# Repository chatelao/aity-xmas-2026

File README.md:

# AITY Xmas Tree 2026

An interactive Christmas tree PCB designed to work with either a **Seeed Studio XIAO RP2040** or a **Seeed Studio XIAO ESP32-C6** microcontroller module, featuring 60 addressable NeoPixel LEDs, a piezo speaker/buzzer, and test point outputs.

## Hardware Specifications

- **Microcontroller:** Seeed Studio XIAO RP2040 or Seeed Studio XIAO ESP32-C6
- **LEDs:** 60 x WS2812B NeoPixel RGB LEDs connected to pin `D10`
- **Audio:** Speaker/Buzzer connected to pin `D0`
- **Test Points:** TP101 – TP109 connected to pins `D1` – `D9`

## ASCII Pinout Diagram

Both XIAO boards share the same standard XIAO form factor and 14-pin pinout:

```
                       +-------------------+
                       |   USB-C           |
                       |  [ Seeed XIAO ]   |
                       | [RP2040/ESP32-C6] |
(Speaker LS101) D0/A0 -| [1]          [14] |- 5V (VDD Power)
 (TestPoint 1)  D1/A1 -| [2]          [13] |- GND
 (TestPoint 3)  D2/A2 -| [3]          [12] |- 3V3 (NC)
 (TestPoint 4)  D3/A3 -| [4]          [11] |- D10/MOSI (60 x NeoPixel LEDs)
 (TestPoint 5) D4/SDA -| [5]          [10] |- D9/MISO  (TestPoint 2)
 (TestPoint 8) D5/SCL -| [6]           [9] |- D8/SCK   (TestPoint 7)
 (TestPoint 6)  D6/TX -| [7]           [8] |- D7/RX    (TestPoint 9)
                       +-------------------+
```

### Pin Mapping Table

| Pin Number | XIAO Pin Name | RP2040 GPIO | ESP32-C6 GPIO | CircuitPython Pin | Connection / Function |
|------------|---------------|-------------|---------------|-------------------|-----------------------|
| 1          | A0 / D0       | GPIO26      | GPIO0 / PA02  | `board.D0`        | Speaker (LS101)       |
| 2          | A1 / D1       | GPIO27      | GPIO1 / PA04  | `board.D1`        | TestPoint 1 (TP101)   |
| 3          | A2 / D2       | GPIO28      | GPIO2 / PA10  | `board.D2`        | TestPoint 3 (TP103)   |
| 4          | A3 / D3       | GPIO29      | GPIO3 / PA11  | `board.D3`        | TestPoint 4 (TP104)   |
| 5          | SDA / D4      | GPIO6       | GPIO19 / PA08 | `board.D4`        | TestPoint 5 (TP105)   |
| 6          | SCL / D5      | GPIO7       | GPIO20 / PA09 | `board.D5`        | TestPoint 8 (TP108)   |
| 7          | TX / D6       | GPIO0       | GPIO21 / PB08 | `board.D6`        | TestPoint 6 (TP106)   |
| 8          | RX / D7       | GPIO1       | GPIO22 / PB09 | `board.D7`        | TestPoint 9 (TP109)   |
| 9          | SCK / D8      | GPIO2       | GPIO23 / PA07 | `board.D8`        | TestPoint 7 (TP107)   |
| 10         | MISO / D9     | GPIO4       | GPIO9 / PA05  | `board.D9`        | TestPoint 2 (TP102)   |
| 11         | MOSI / D10    | GPIO3       | GPIO18 / PA06 | `board.D10`       | NeoPixel LEDs Data In |
| 12         | 3V3           | 3V3         | 3V3           | `board.3V3`       | Unconnected (NC)      |
| 13         | GND           | GND         | GND           | `board.GND`       | Ground                |
| 14         | 5V            | 5V          | 5V            | `board.5V`        | 5V Power (VDD)        |

---

## Platform Setup & Installation Guides

Detailed instructions on how to install CircuitPython (web-only method) and transfer files (via web browser or file explorer) for each platform:

- [**HOWTO_RP2040.md**](HOWTO_RP2040.md) — Guide for **Seeed Studio XIAO RP2040**
- [**HOWTO_ESP32-C6.md**](HOWTO_ESP32-C6.md) — Guide for **Seeed Studio XIAO ESP32-C6**

---

## Example CircuitPython Script: Rainbow Animation

Save the following script as `code.py` or `main.py` on the target device. Make sure the Adafruit `neopixel` library (`neopixel.mpy`) is placed in the `lib/` folder.

```python
import time
import board
import neopixel

# Try importing built-in colorwheel from rainbowio, fallback if not present
try:
    from rainbowio import colorwheel
except ImportError:
    def colorwheel(pos):
        """Generate rainbow colors across 0-255 positions."""
        pos = int(pos) % 256
        if pos < 85:
            return (pos * 3, 255 - pos * 3, 0)
        elif pos < 170:
            pos -= 85
            return (255 - pos * 3, 0, pos * 3)
        else:
            pos -= 170
            return (0, pos * 3, 255 - pos * 3)

# Configuration
NUM_LEDS = 60
DATA_PIN = board.D10
BRIGHTNESS = 0.3  # Adjust brightness (0.0 to 1.0)

# Initialize NeoPixel strip
pixels = neopixel.NeoPixel(
    DATA_PIN,
    NUM_LEDS,
    brightness=BRIGHTNESS,
    auto_write=False
)

def rainbow_cycle(wait=0.01):
    """Animate a smooth moving rainbow across all 60 LEDs."""
    for j in range(256):
        for i in range(NUM_LEDS):
            pixel_index = (i * 256 // NUM_LEDS) + j
            pixels[i] = colorwheel(pixel_index & 255)
        pixels.show()
        time.sleep(wait)

print("Starting Rainbow Animation on 60 NeoPixel LEDs...")

while True:
    rainbow_cycle(wait=0.01)
```

## Setup Instructions

1. Install CircuitPython on your board (see [HOWTO_RP2040.md](HOWTO_RP2040.md) for XIAO RP2040 or [HOWTO_ESP32-C6.md](HOWTO_ESP32-C6.md) for XIAO ESP32-C6).
2. Obtain the Adafruit CircuitPython Library Bundle (or use the pre-packaged files in `circuitpython/default/`).
3. Copy `neopixel.mpy` into the `lib/` directory on the target board (using file explorer for RP2040 or web workflow for ESP32-C6).
4. Save the example script above (or `circuitpython/default/code.py`) as `code.py` on the target board.

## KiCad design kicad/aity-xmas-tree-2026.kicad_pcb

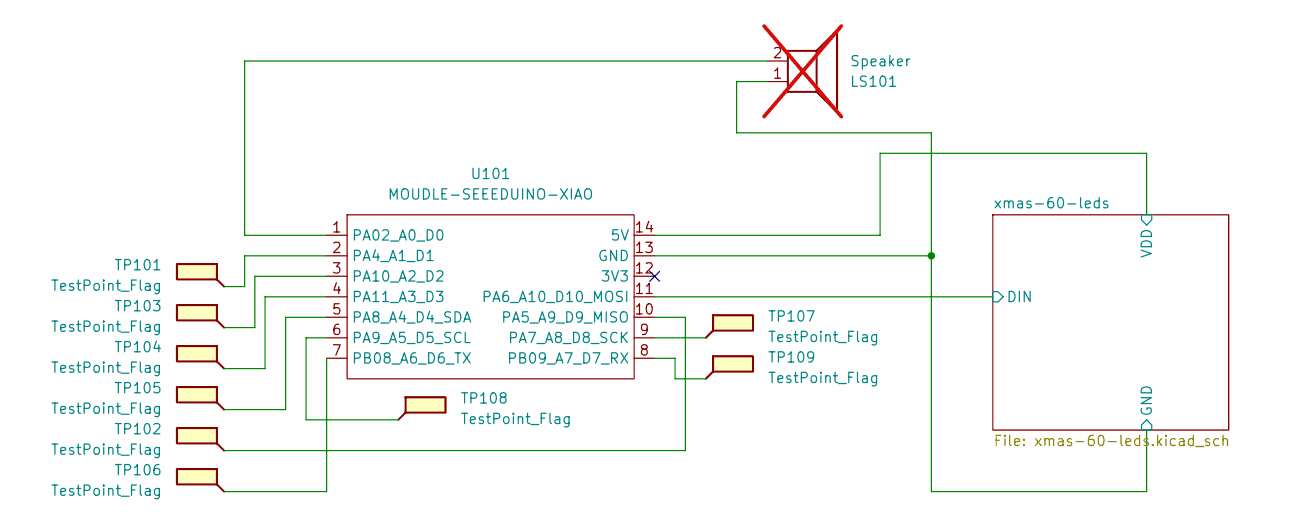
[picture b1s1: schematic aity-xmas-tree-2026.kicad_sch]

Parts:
LS101: Speaker; MagneticBuzzer_CUI_CMT-8504-100-SMT; not fitted
TP101, TP102, TP103, TP104, TP105, TP106, TP107, TP108, TP109: TestPoint_Flag; Kugel
U101: MOUDLE-SEEEDUINO-XIAO; MCU_Seeed_ESP32C3

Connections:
/xmas-60-leds/DIN: U101.11 (PA6_A10_D10_MOSI); also elsewhere on the board
/xmas-60-leds/GND: LS101.1, U101.13 (GND); also elsewhere on the board
/xmas-60-leds/VDD: U101.14 (5V); also elsewhere on the board
unnamed: LS101.2, U101.1 (PA02_A0_D0)
unnamed: TP101.1, U101.2 (PA4_A1_D1)
unnamed: TP102.1, U101.10 (PA5_A9_D9_MISO)
unnamed: TP107.1, U101.9 (PA7_A8_D8_SCK)
unnamed: TP105.1, U101.5 (PA8_A4_D4_SDA)
unnamed: TP108.1, U101.6 (PA9_A5_D5_SCL)
unnamed: TP103.1, U101.3 (PA10_A2_D2)
unnamed: TP104.1, U101.4 (PA11_A3_D3)
unnamed: TP106.1, U101.7 (PB08_A6_D6_TX)
unnamed: TP109.1, U101.8 (PB09_A7_D7_RX)

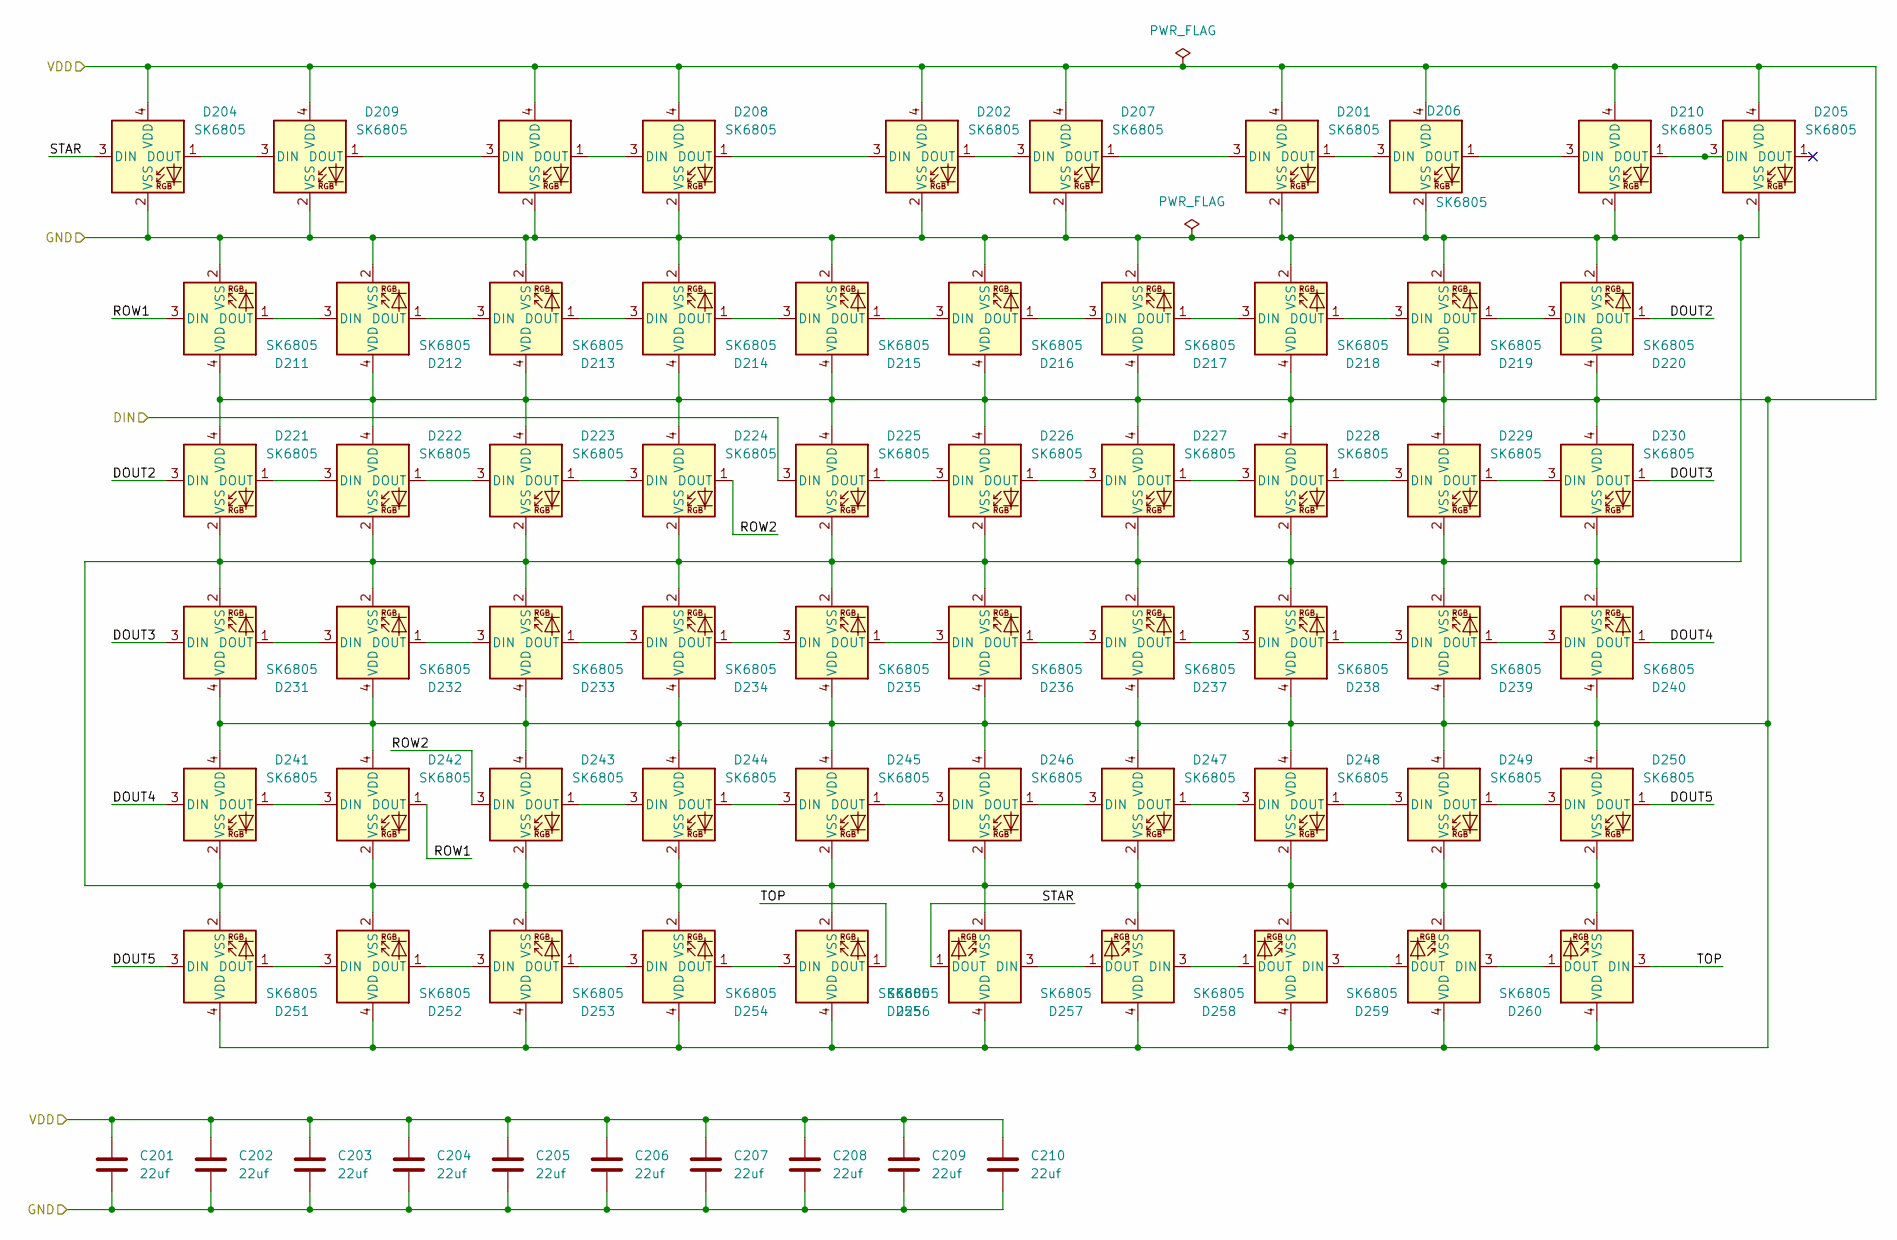
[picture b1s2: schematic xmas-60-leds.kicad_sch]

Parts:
C201, C202, C203, C204, C205, C206, C207, C208, C209, C210: 22uf; C_0603_1608Metric
D201, D203, D204, D205, D207, D208, D209, D210, D211, D212, D213, D214, D215, D216, D217, D218, D219, D220, D221, D222, D223, D224, D225, D226, D227, D228, D229, D230, D231, D232, D233, D234, D235, D236, D237, D238, D239, D240, D241, D242, D243, D244, D245, D246, D247, D248, D249, D250, D251, D252, D253, D254, D255, D256, D257, D258, D259, D260: SK6805; LED_SK6812_1.5x1.5mm
D202, D206: SK6805; LED_SK6805_PLCC4_2.4x2.7mm_P1.3mm

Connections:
/xmas-60-leds/DIN: D225.3 (DIN); also elsewhere on the board
/xmas-60-leds/DOUT2: D220.1 (DOUT), D221.3 (DIN)
/xmas-60-leds/DOUT3: D230.1 (DOUT), D231.3 (DIN)
/xmas-60-leds/DOUT4: D240.1 (DOUT), D241.3 (DIN)
/xmas-60-leds/DOUT5: D250.1 (DOUT), D251.3 (DIN)
/xmas-60-leds/GND: C201.2, C202.2, C203.2, C204.2, C205.2, C206.2, C207.2, C208.2, C209.2, C210.2, D201.2 (VSS), D202.2 (VSS), D203.2 (VSS), D204.2 (VSS), D205.2 (VSS), D206.2 (VSS), D207.2 (VSS), D208.2 (VSS), D209.2 (VSS), D210.2 (VSS), D211.2 (VSS), D212.2 (VSS), D213.2 (VSS), D214.2 (VSS), D215.2 (VSS), D216.2 (VSS), D217.2 (VSS), D218.2 (VSS), D219.2 (VSS), D220.2 (VSS), D221.2 (VSS), D222.2 (VSS), D223.2 (VSS), D224.2 (VSS), D225.2 (VSS), D226.2 (VSS), D227.2 (VSS), D228.2 (VSS), D229.2 (VSS), D230.2 (VSS), D231.2 (VSS), D232.2 (VSS), D233.2 (VSS), D234.2 (VSS), D235.2 (VSS), D236.2 (VSS), D237.2 (VSS), D238.2 (VSS), D239.2 (VSS), D240.2 (VSS), D241.2 (VSS), D242.2 (VSS), D243.2 (VSS), D244.2 (VSS), D245.2 (VSS), D246.2 (VSS), D247.2 (VSS), D248.2 (VSS), D249.2 (VSS), D250.2 (VSS), D251.2 (VSS), D252.2 (VSS), D253.2 (VSS), D254.2 (VSS), D255.2 (VSS), D256.2 (VSS), D257.2 (VSS), D258.2 (VSS), D259.2 (VSS), D260.2 (VSS); also elsewhere on the board
/xmas-60-leds/ROW1: D211.3 (DIN), D242.1 (DOUT)
/xmas-60-leds/ROW2: D224.1 (DOUT), D243.3 (DIN)
/xmas-60-leds/STAR: D204.3 (DIN), D256.1 (DOUT)
/xmas-60-leds/TOP: D255.1 (DOUT), D260.3 (DIN)
/xmas-60-leds/VDD: C201.1, C202.1, C203.1, C204.1, C205.1, C206.1, C207.1, C208.1, C209.1, C210.1, D201.4 (VDD), D202.4 (VDD), D203.4 (VDD), D204.4 (VDD), D205.4 (VDD), D206.4 (VDD), D207.4 (VDD), D208.4 (VDD), D209.4 (VDD), D210.4 (VDD), D211.4 (VDD), D212.4 (VDD), D213.4 (VDD), D214.4 (VDD), D215.4 (VDD), D216.4 (VDD), D217.4 (VDD), D218.4 (VDD), D219.4 (VDD), D220.4 (VDD), D221.4 (VDD), D222.4 (VDD), D223.4 (VDD), D224.4 (VDD), D225.4 (VDD), D226.4 (VDD), D227.4 (VDD), D228.4 (VDD), D229.4 (VDD), D230.4 (VDD), D231.4 (VDD), D232.4 (VDD), D233.4 (VDD), D234.4 (VDD), D235.4 (VDD), D236.4 (VDD), D237.4 (VDD), D238.4 (VDD), D239.4 (VDD), D240.4 (VDD), D241.4 (VDD), D242.4 (VDD), D243.4 (VDD), D244.4 (VDD), D245.4 (VDD), D246.4 (VDD), D247.4 (VDD), D248.4 (VDD), D249.4 (VDD), D250.4 (VDD), D251.4 (VDD), D252.4 (VDD), D253.4 (VDD), D254.4 (VDD), D255.4 (VDD), D256.4 (VDD), D257.4 (VDD), D258.4 (VDD), D259.4 (VDD), D260.4 (VDD); also elsewhere on the board
unnamed: D201.3 (DIN), D207.1 (DOUT)
unnamed: D201.1 (DOUT), D206.3 (DIN)
unnamed: D202.3 (DIN), D208.1 (DOUT)
unnamed: D202.1 (DOUT), D207.3 (DIN)
unnamed: D203.3 (DIN), D209.1 (DOUT)
unnamed: D203.1 (DOUT), D208.3 (DIN)
unnamed: D204.1 (DOUT), D209.3 (DIN)
unnamed: D205.3 (DIN), D210.1 (DOUT)
unnamed: D206.1 (DOUT), D210.3 (DIN)
unnamed: D211.1 (DOUT), D212.3 (DIN)
unnamed: D212.1 (DOUT), D213.3 (DIN)
unnamed: D213.1 (DOUT), D214.3 (DIN)
unnamed: D214.1 (DOUT), D215.3 (DIN)
unnamed: D215.1 (DOUT), D216.3 (DIN)
unnamed: D216.1 (DOUT), D217.3 (DIN)
unnamed: D217.1 (DOUT), D218.3 (DIN)
unnamed: D218.1 (DOUT), D219.3 (DIN)
unnamed: D219.1 (DOUT), D220.3 (DIN)
unnamed: D221.1 (DOUT), D222.3 (DIN)
unnamed: D222.1 (DOUT), D223.3 (DIN)
unnamed: D223.1 (DOUT), D224.3 (DIN)
unnamed: D225.1 (DOUT), D226.3 (DIN)
unnamed: D226.1 (DOUT), D227.3 (DIN)
unnamed: D227.1 (DOUT), D228.3 (DIN)
unnamed: D228.1 (DOUT), D229.3 (DIN)
unnamed: D229.1 (DOUT), D230.3 (DIN)
unnamed: D231.1 (DOUT), D232.3 (DIN)
unnamed: D232.1 (DOUT), D233.3 (DIN)
unnamed: D233.1 (DOUT), D234.3 (DIN)
unnamed: D234.1 (DOUT), D235.3 (DIN)
unnamed: D235.1 (DOUT), D236.3 (DIN)
unnamed: D236.1 (DOUT), D237.3 (DIN)
unnamed: D237.1 (DOUT), D238.3 (DIN)
unnamed: D238.1 (DOUT), D239.3 (DIN)
unnamed: D239.1 (DOUT), D240.3 (DIN)
unnamed: D241.1 (DOUT), D242.3 (DIN)
unnamed: D243.1 (DOUT), D244.3 (DIN)
unnamed: D244.1 (DOUT), D245.3 (DIN)
unnamed: D245.1 (DOUT), D246.3 (DIN)
unnamed: D246.1 (DOUT), D247.3 (DIN)
unnamed: D247.1 (DOUT), D248.3 (DIN)
unnamed: D248.1 (DOUT), D249.3 (DIN)
unnamed: D249.1 (DOUT), D250.3 (DIN)
unnamed: D251.1 (DOUT), D252.3 (DIN)
unnamed: D252.1 (DOUT), D253.3 (DIN)
unnamed: D253.1 (DOUT), D254.3 (DIN)
unnamed: D254.1 (DOUT), D255.3 (DIN)
unnamed: D256.3 (DIN), D257.1 (DOUT)
unnamed: D257.3 (DIN), D258.1 (DOUT)
unnamed: D258.3 (DIN), D259.1 (DOUT)
unnamed: D259.3 (DIN), D260.1 (DOUT)

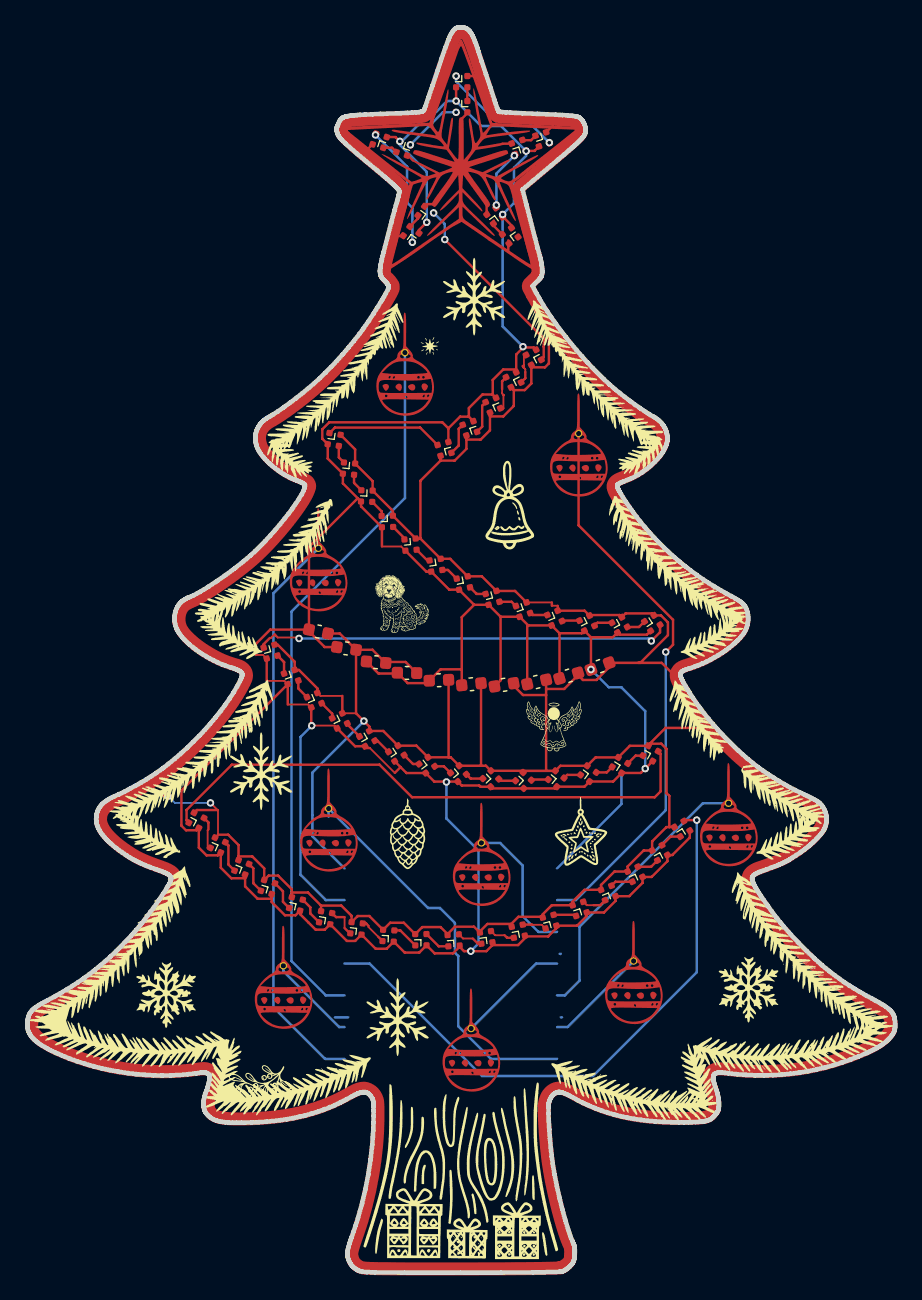
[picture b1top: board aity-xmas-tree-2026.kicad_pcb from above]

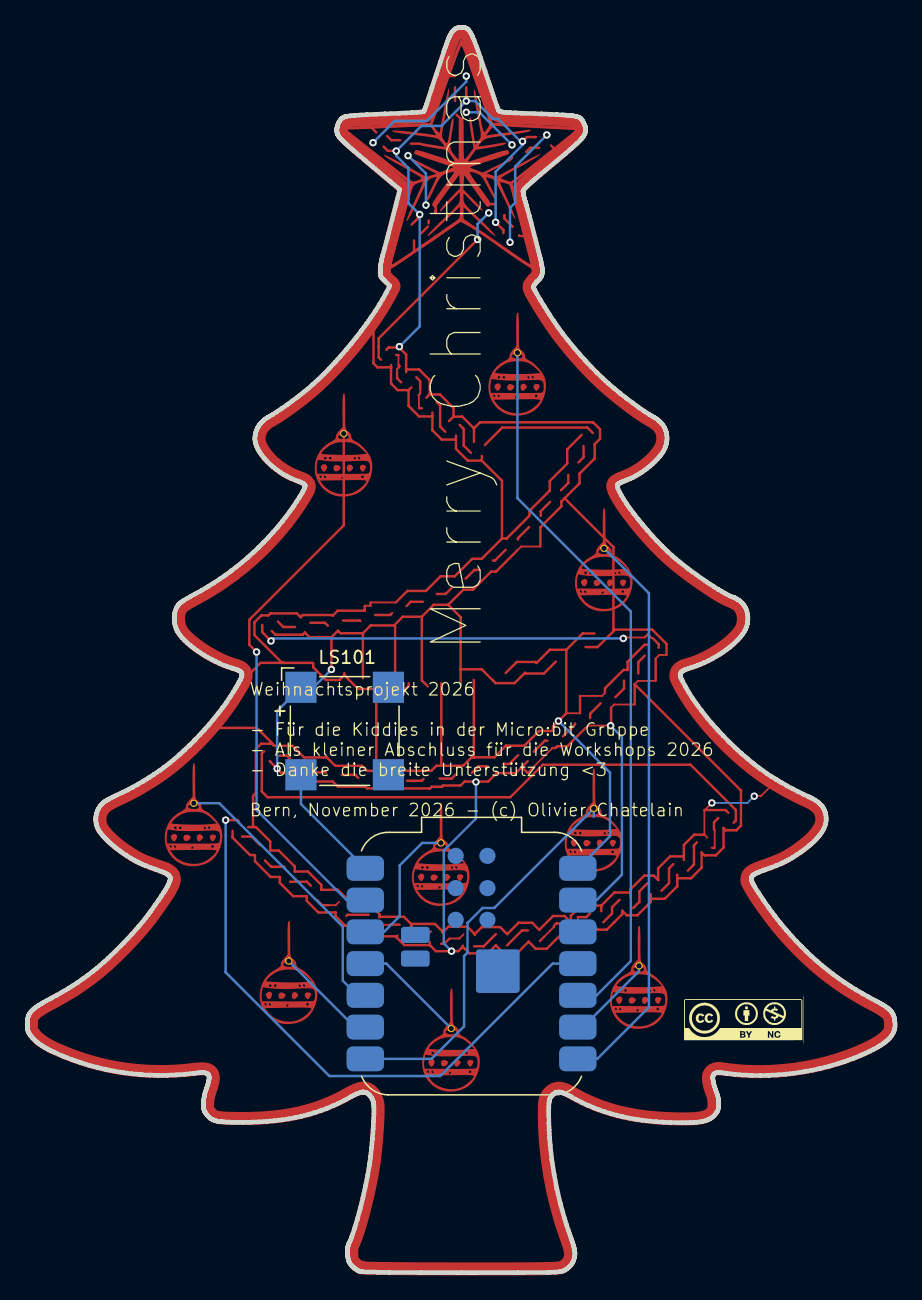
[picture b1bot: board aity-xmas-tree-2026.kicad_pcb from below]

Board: 2 copper layers, 69.4 x 99.6 mm, 81 parts (2 on the bottom side), 72 nets.
